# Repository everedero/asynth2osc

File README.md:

# Bad, bad version of the analog synthesizer to Open Sound Control (OSC) module

## Project description

See branch main for the real project description.

On this branch, we modify the working design, to make a test project for automatic review tools.

Do not use it for reference. Do not copy it. Absolutely never send it to production.
This is a design full of mistakes for the sake of finding mistakes.

## Error list

### LAN8742A PHY
* VDDCR is 1.2V LDO output, should not be connected to 3V3.
* nINTSEL/LED2 should be pulled down, to 0. Or we should have a 50 MHz clock instead of 25 MHz.
  * INT/REF\_CLK\_OUT in this schematics look like it is used to generate the 50MHz clock for RMII,
    not as interrupt.
  * LED R80 on the connector should be pulled down to match the inversion.
* RX\_S\_N and RX\_S\_P on U11 (USB ESD diodes) are inverted.
* RBIAS R58 is 51k, it should be 12.1k.

### Interface
* SW7 and SW8 LED has no serial resistor, directly connected to 3V3. Should have a min 68 ohms.
* R82 should be around 1Mohms, not 10k, for the OLED display, as the comment says.

### Supply
* The fuse is short-circuited, net name VBUS should be modified.
* No protection against plugging the Eurorack connector the wrong way round: -12V instead of +12V
  would damage the board. A diode would be great.
* LDO U1 (LM1117M) LCSC reference is for a 5V LDO, it should be a 3V3.

### STM32H7 SoC
* Cannot setup different interrupts for GPIO (EXTI register) having the same numbers but on different ports.
  A comment specifically says the buttons should be interrupts.
    * See [this issue](https://github.com/zephyrproject-rtos/zephyr/issues/45234).
    * Issue with A8 rotative encoder pushbutton VS C8 rotary input B.
    * Issue with D14 rotary input A and E14 trig input.
* Capacitor C23 and C24 should be much lower than 100nF, 4.3pF for instance.
* STM32 NRST pin is not connected, not to a button, not to any debugger pin.
* STM32 Value, RefNum and LCSC number are for the 144 pin version (STM32H723\_Z\_GT instead
  of STM32H723\_V\_GT)

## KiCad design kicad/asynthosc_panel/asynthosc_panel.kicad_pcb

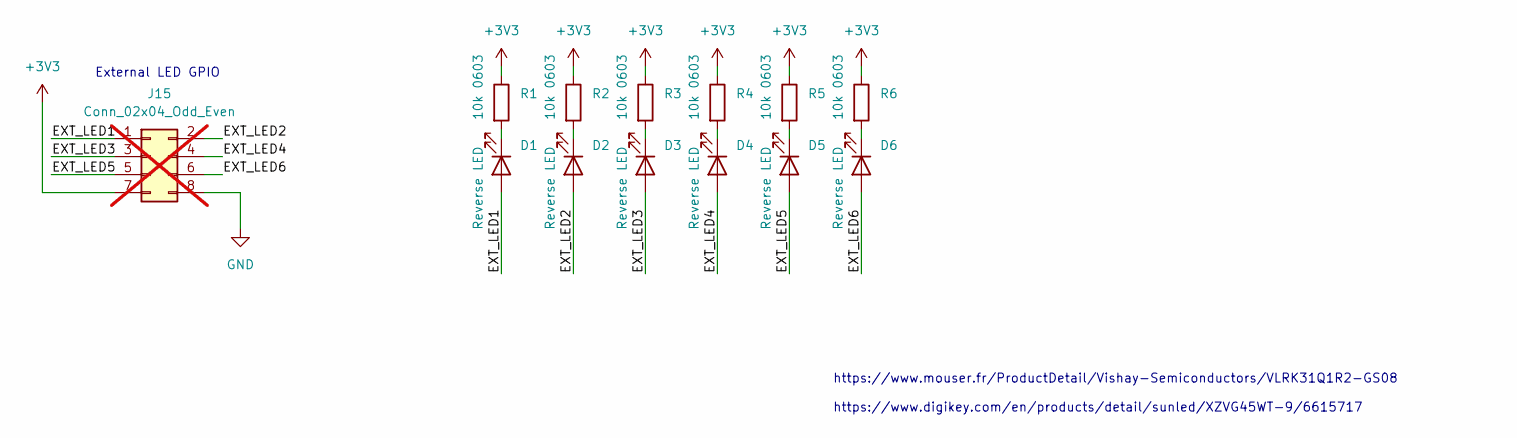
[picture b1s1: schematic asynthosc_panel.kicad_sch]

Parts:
D1, D2, D3, D4, D5, D6: Reverse LED; LED_Sunled_XZxx45x-9_nohole
J15: Conn_02x04_Odd_Even; PinHeader_2x04_P2.54mm_Vertical_SMD; LCSC C192300; not fitted
R1, R2, R3, R4, R5, R6: 10k 0603; R_0603_1608Metric_Pad0.98x0.95mm_HandSolder

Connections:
+3V3: J15.7, R1.1, R2.1, R3.1, R4.1, R5.1, R6.1
/EXT_LED1: D1.2 (A), J15.1
/EXT_LED2: D2.2 (A), J15.2
/EXT_LED3: D3.2 (A), J15.3
/EXT_LED4: D4.2 (A), J15.4
/EXT_LED5: D5.2 (A), J15.5
/EXT_LED6: D6.2 (A), J15.6
GND: J15.8
unnamed: D1.1 (K), R1.2
unnamed: D2.1 (K), R2.2
unnamed: D3.1 (K), R3.2
unnamed: D4.1 (K), R4.2
unnamed: D5.1 (K), R5.2
unnamed: D6.1 (K), R6.2

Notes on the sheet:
https://www.mouser.fr/ProductDetail/Vishay-Semiconductors/VLRK31Q1R2-GS08 https://www.digikey.com/en/products/detail/sunled/XZVG45WT-9/6615717
External LED GPIO

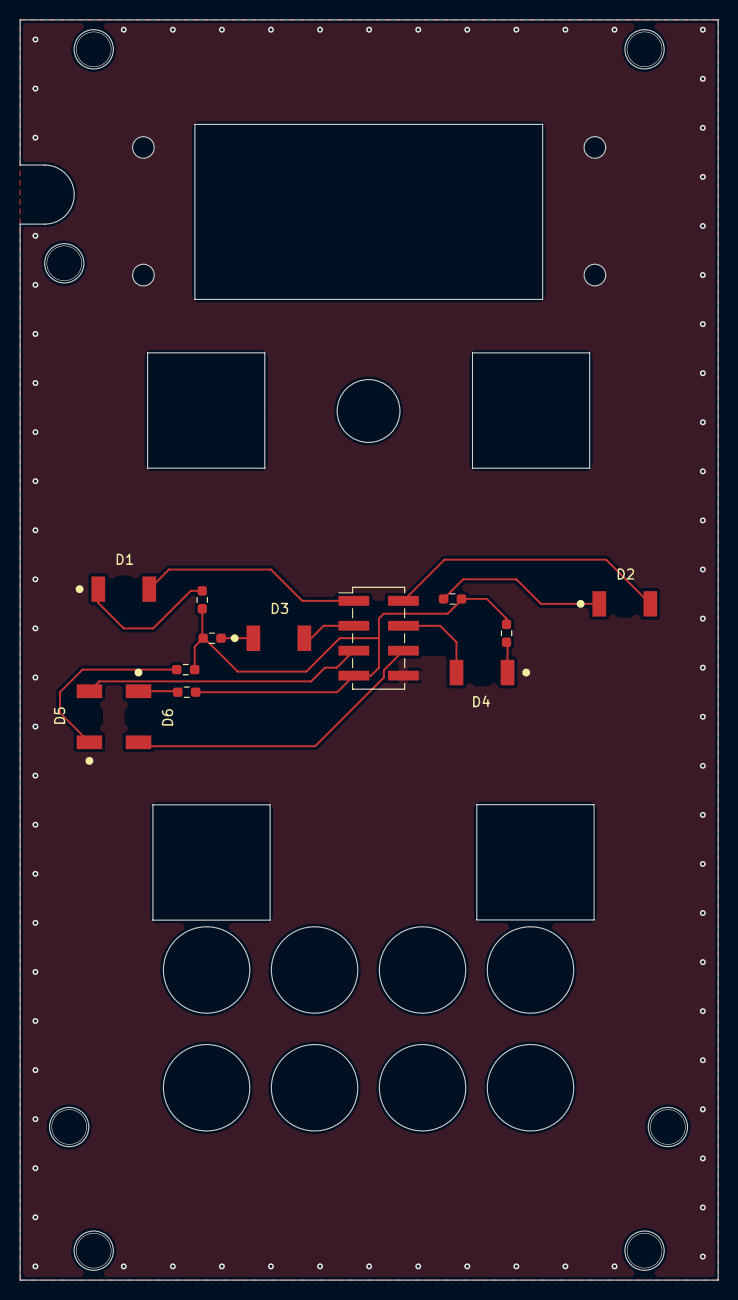
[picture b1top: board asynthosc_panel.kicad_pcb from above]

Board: 2 copper layers, 71.1 x 128.4 mm, 13 parts (0 on the bottom side), 13 nets.

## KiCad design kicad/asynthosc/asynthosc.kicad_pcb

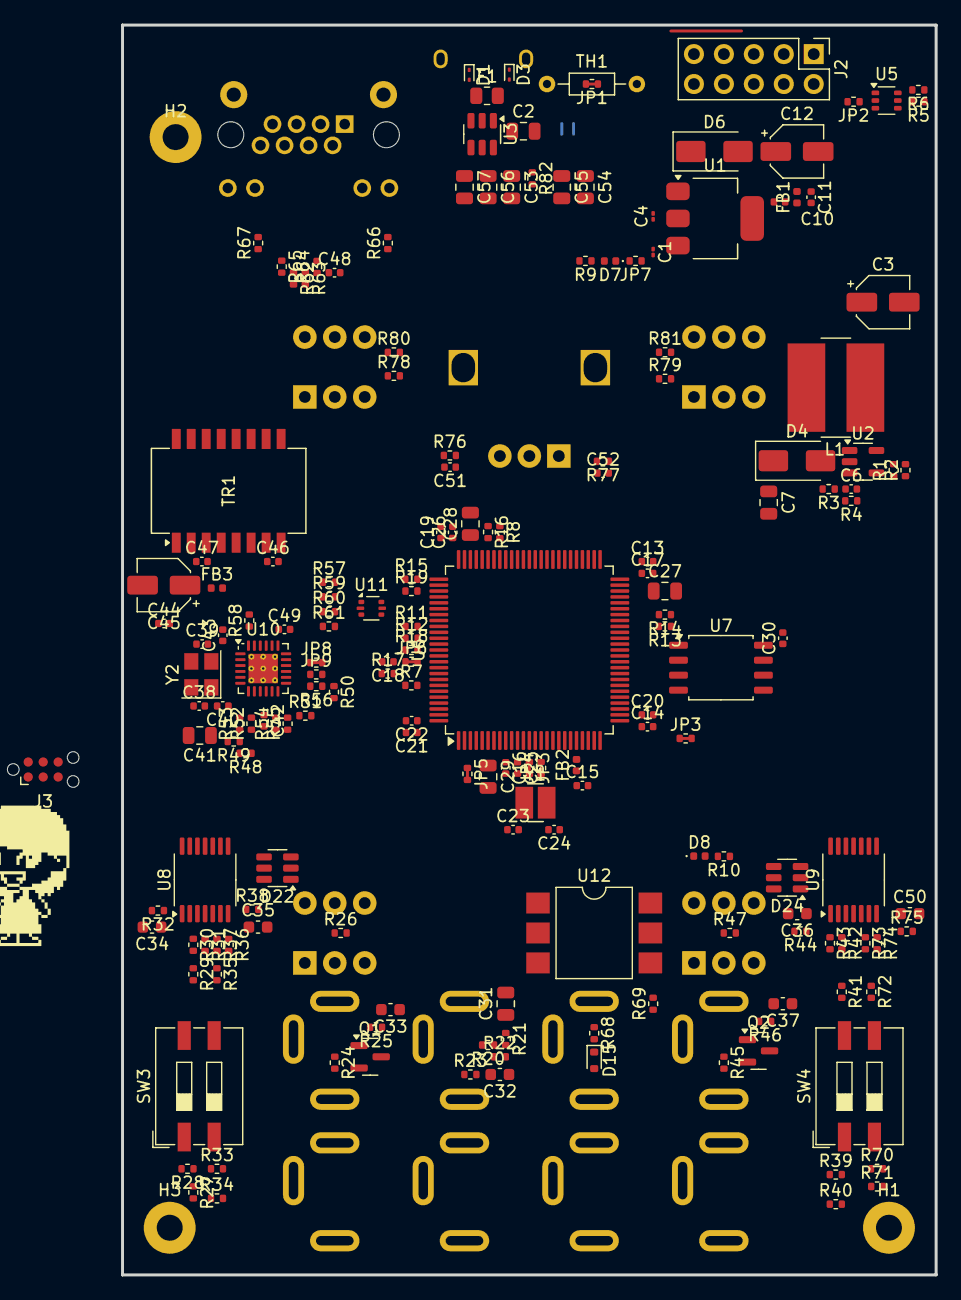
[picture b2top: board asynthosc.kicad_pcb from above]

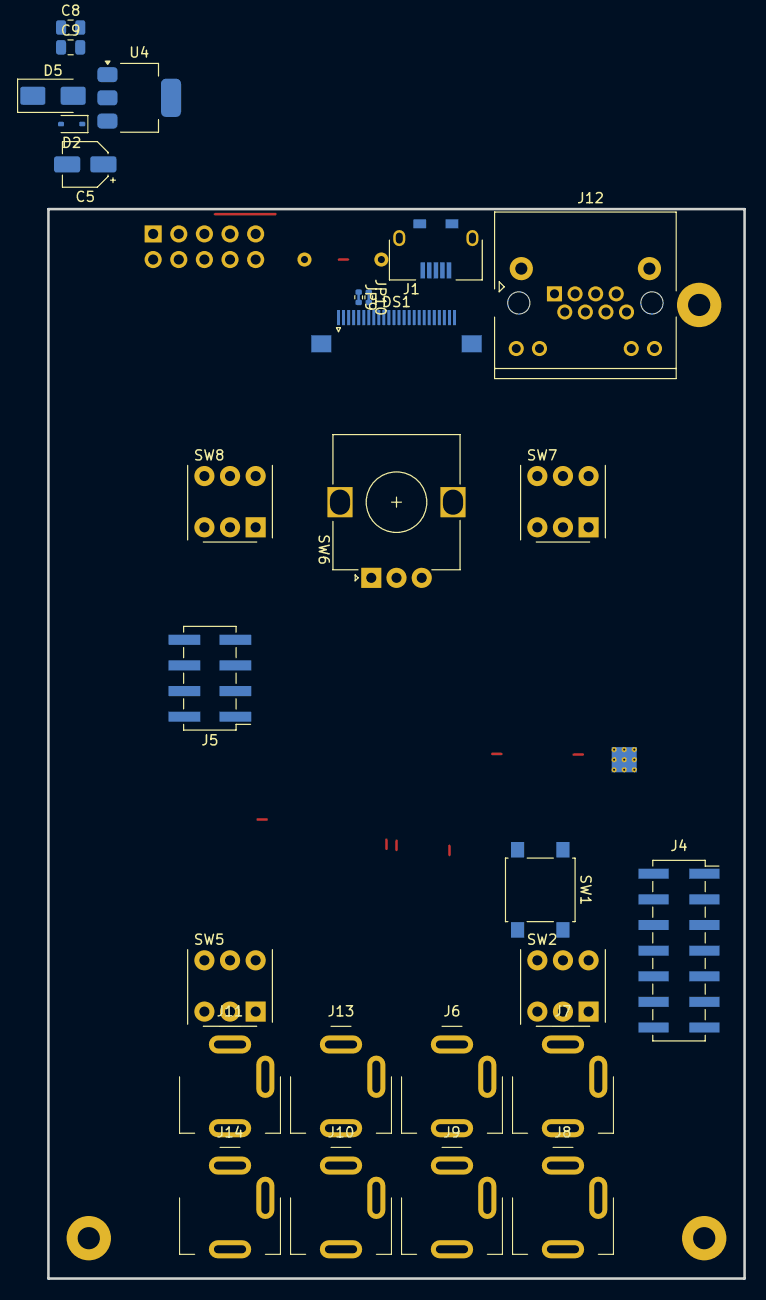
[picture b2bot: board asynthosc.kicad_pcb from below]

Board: 4 copper layers, 69.0 x 106.0 mm, 211 parts (27 on the bottom side), 144 nets, no tracks yet.

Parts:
C1, C4: 100nF; C_01005_0402Metric
C2, C8, C9: 100nF; C_0805_2012Metric
C3, C5, C12, C45: 10uF; CP_Elec_4x5.4
C6: 680pF; C_0402_1005Metric
C7: 47uF / 3.037mOhms; C_0805_2012Metric
C10: 10nF; C_0402_1005Metric
C11, C13, C14, C15, C16, C17, C18, C19, C20, C21, C22, C25, C26, C30, C42, C43, C44, C46, C47, C49, C51, C52: 100nF; C_0402_1005Metric
C23, C24: 4.3pF; C_0402_1005Metric
C27, C28: 2.2u X7R; C_0805_2012Metric
C29, C41: 1uF; C_0805_2012Metric
C31: 10uF; C_0805_2012Metric
C32: 18pF; C_0603_1608Metric
C33, C37: 100nF; C_0603_1608Metric
C34, C35, C36, C50: 1nF; C_0603_1608Metric
C38, C39: 30pF; C_0402_1005Metric
C40: 470pF; C_0402_1005Metric
C48: 1000pF X7R; C_0402_1005Metric
C53: 2.2uF/25V; C_0805_2012Metric
C54, C55: 1uF / 16V; C_0805_2012Metric
C56: 4.7uF/25V/X7R; C_0805_2012Metric
C57: 0.1uF/25V/X7R; C_0805_2012Metric
D1, D3: ESD9B5.0ST5G; D_SOD-923
D2: 1N5819WS; D_SOD-323
D4, D5, D6: SS24; D_SMA
D7, D8: LED; LED_0402_1005Metric
D15: 1N4148WT; D_SOD-523
D22, D24: D_Schottky_Dual_SD103ASDM; SOT-23-6
DS1: OLED Connector 128x64; HRO_FPC0.5B-WTG-24P_1x24-1MP_P0.5mm_Horizontal
F1: Fuse, 1.25A, trip 2.5A; R_0805_2012Metric
FB1, FB2, FB3: BLM15PX330SN1D; L_0402_1005Metric
H1, H2, H3: MountingHole_Pad; MountingHole_2.2mm_M2_Pad
J1: USB_B_Micro; USB_Micro-B_Shou-han-MicroXNJ
J2: Conn_02x05_Odd_Even; PinHeader_2x05_P2.54mm_Vertical
J3: Conn_ARM_SWD_TagConnect_TC2030-NL; Tag-Connect_TC2030-IDC-NL_2x03_P1.27mm_Vertical
J4: Conn_02x07_Odd_Even; PinSocket_2x07_P2.54mm_Vertical_SMD
J5: Conn_02x04_Odd_Even; PinHeader_2x04_P2.54mm_Vertical_SMD
J6, J7, J8, J9, J10, J11, J13, J14: AudioJack3; Jack_3.5mm_3legs_XKB_PJ-3411_Vertical
J12: RJ45_LED_Shielded; RJ45_HCTL_HC-RJ45-053-2
JP1, JP3, JP3#2, JP4, JP5, JP6, JP8, JP9#2, JP10: SolderJumper_2_Bridged; SolderJumper_0402_1005Metric_Bridged
JP2, JP7, JP9: SolderJumper_2_Open; R_0402_1005Metric
L1: 8.2uH / 80mOhm; L_XR_XRCD75-XRX_7x7.8
Q1, Q2: Q_NPN_BEC; SOT-23
R1, R2, R3, R5, R6, R8, R25, R46, R76, R77, R78, R79: 10k; R_0402_1005Metric
R4: 69.8k; R_0402_1005Metric
R7, R24, R29, R30, R35, R36, R41, R42, R45, R48, R49, R50, R72, R73: 100k; R_0402_1005Metric
R9, R10, R26, R47, R66, R67, R80, R81: 270R; R_0402_1005Metric
R11, R12, R13, R14, R15, R16, R17, R18, R19: 22R; R_0402_1005Metric
R20, R22: 39k; R_0402_1005Metric
R21: 5.6k; R_0402_1005Metric
R23: 1k; R_0402_1005Metric
R27, R33, R39, R70: 47k; R_0402_1005Metric
R28, R31, R32, R34, R37, R38, R40, R43, R44, R71, R74, R75: 33k; R_0402_1005Metric
R51: 1.5K; R_0402_1005Metric
R52, R53, R54, R55, R56: 33R; R_0402_1005Metric
R57, R59, R60, R61: 50R; R_0402_1005Metric
R58: 12.1k; R_0402_1005Metric
R62, R63, R64, R65: 75R; R_0402_1005Metric
R68, R69: 220; R_0402_1005Metric
R82: 1M; R_0402_1005Metric
SW1: SW_Push; SW_SPST_B3S-1000
SW2, SW5, SW7, SW8: SW_MEC_5G_LED; TPB01-X0XLXX_SW_MEC_5G
SW3, SW4: SW_DIP_x02; SW_DIP_SPSTx02_Slide_9.78x7.26mm_W8.61mm_P2.54mm
SW6: RotaryEncoder; RotaryEncoder_Alps_EC12E_Vertical_H20mm
TH1: Thermistor_NTC; R_Axial_DIN0204_L3.6mm_D1.6mm_P7.62mm_Horizontal
TR1: PT61017PEL; Transformer_Ethernet_Bourns_PT61017PEL
U1: LM1117S-3.3; SOT-223
U2: LMR62421XMF; SOT-23-5
U3: USBLC6-2SC6; SOT-23-6
U4: LM1117S-5.0; SOT-223
U5: Si1869DH; SOT-363_SC-70-6
U6: STM32F723VETx; LQFP-100_14x14mm_P0.5mm
U7: W25Q32JVSS; SOIC-8_5.23x5.23mm_P1.27mm
U8, U9: MCP6004; TSSOP-14_4.4x5mm_P0.65mm
U10: LAN8742A; VQFN-24-1EP_4x4mm_P0.5mm_EP2.5x2.5mm_ThermalVias
U11: USBLC6-2P6; SOT-666
U12: H11L1; SMDIP-6_W9.53mm
Y1: 8MHz, 8pF; Crystal_SMD_3225-2Pin_3.2x2.5mm
Y2: 25MHZ,20PF,30PPM; Crystal_SMD_3225-4Pin_3.2x2.5mm

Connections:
3V3: C4.1, C13.1, C14.1, C15.1, C16.1, C17.1, C19.1, C20.1, C21.1, C22.1, C25.1, C26.1, C30.1, C40.1, C41.1, C42.1, C54.1, C55.1, D22.2 (K), D22.5 (K), D24.2 (K), D24.5 (K), DS1.5 (VDD), FB2.1, FB3.2, J3.1 (VCC), J4.2, JP5.2 (B), R9.1, R10.1, R25.2, R46.2, R48.2, R49.2, R50.2, R51.2, R69.1, R76.1, R77.1, R78.1, R79.1, R80.1, R81.1, U1.2 (VO), U6.11 (VDD), U6.27 (VDD), U6.50 (VDD), U6.75 (VDD), U6.100 (VDD), U7.8 (VCC), U10.6 (VDDCR), U10.9 (VDDIO), U12.6
3V3_FILT: C43.1, C44.1, C45.1, C46.1, C47.1, C49.1, FB3.1, R57.2, R59.2, R60.2, R61.2, TR1.2 (C_TD), TR1.7 (C_RD), U10.1 (VDD2A), U10.19 (VDD1A), U11.5 (VBUS)
5V: C1.1, D5.1 (K), D6.1 (K), R30.2, R36.2, R42.2, R73.2, U1.3 (VI), U8.4 (V+), U9.4 (V+)
+10V: C6.2, C7.1, C56.1, C57.1, D4.1 (K), DS1.23 (VCC), JP2.2 (B), R4.1
/Analog_in/CVIN0: C34.1, D22.6 (common), R32.1, U6.22 (PA0), U8.1
/Analog_in/CVIN1: C35.1, D22.3 (common), R38.1, U6.25 (PA3), U8.7
/Analog_in/CVIN2: C36.1, D24.6 (common), R44.1, U6.29 (PA5), U9.1
/Analog_in/CVIN3: C50.1, D24.3 (common), R75.1, U6.30 (PA6), U9.7
/Analog_in/TRG0: C37.2, Q2.3 (C), R46.1, SW5.1, SW5.3 (K)
/Analog_in/TRG1: C33.2, Q1.3 (C), R25.1, SW2.1, SW2.3 (K), U6.43 (PE13)
/Interface/BTN_1: R78.2, SW7.1
/Interface/BTN_2: R79.2, SW8.1
/Interface/ROT_A: C52.1, R77.2, SW6.A
/Interface/ROT_B: C51.1, R76.2, SW6.B
/Interface/SCLK: DS1.13 (D0), U6.78 (PC10)
/Interface/SDIN: DS1.14 (D1), U6.80 (PC12)
/Midi_in/MIDI_IN+: J13.R, R68.1
/Midi_in/MIDI_IN-: D15.2 (A), J13.T, U12.2
/Midi_in/MIDI_TO_SOC: R69.2, U12.4
/Soc/BOOT0: R7.2, U6.94 (BOOT0)
/Soc/DAC_OUT1: C31.2, U6.28 (PA4)
/Soc/DISP_10V_EN: R1.1, R2.1, U2.4 (EN)
/Soc/Ethernet/RJ45_LED1: J12.12, U10.3 (LED1/REGOFF)
/Soc/Ethernet/RJ45_LED2: J12.10, U10.2 (LED2/~INTSEL)
/Soc/Ethernet/RJ_RX_N: J12.6, R62.2, TR1.15 (C_TX)
/Soc/Ethernet/RJ_RX_P: J12.3, TR1.14 (TX-)
/Soc/Ethernet/RJ_TX_N: J12.2, TR1.11 (RX+)
/Soc/Ethernet/RJ_TX_P: J12.1, TR1.9 (RX-)
/Soc/Ethernet/RX_N: R57.1, TR1.1 (TD+), U10.22 (RXN), U11.6 (I/O1)
/Soc/Ethernet/RX_P: R59.1, TR1.3 (TD-), U10.23 (RXP), U11.1 (I/O1)
/Soc/Ethernet/TX_N: R60.1, TR1.6 (RD+), U10.20 (TXN), U11.4 (I/O2)
/Soc/Ethernet/TX_P: R61.1, TR1.8 (RD-), U10.21 (TXP), U11.3 (I/O2)
/Soc/JTCK: R15.2, U6.76 (PA14)
/Soc/JTCK_CONN: J3.4 (SWCLK), J4.4, R15.1
/Soc/JTDI: R19.2, U6.77 (PA15)
/Soc/JTDI_CONN: J4.14, R19.1
/Soc/JTDO: R18.2, U6.89 (PB3)
/Soc/JTDO_CONN: J3.6 (SWO), J4.12, R18.1
/Soc/JTMS: R16.2, U6.72 (PA13)
/Soc/JTMS_CONN: J3.2 (SWDIO), J4.8, R16.1
/Soc/NRST: C18.1, JP6.1 (A), JP8.2 (B), R17.2, SW1.2, U6.14 (NRST)
/Soc/NRST_CONN: J3.3 (~RESET), J4.10, R17.1
/Soc/QSPI_BK2_IO0: U6.18 (PC3), U7.5 (DI(IO0))
/Soc/QSPI_BK2_IO1: U6.34 (PB0), U7.2 (DO(IO1))
/Soc/QSPI_BK2_IO2: U6.1 (PE2), U7.3 (IO2)
/Soc/QSPI_BK2_IO3: U6.60 (PD13), U7.7 (IO3)
/Soc/QSPI_BK2_NCS: U6.41 (PE11), U7.1 (~CS)
/Soc/QSPI_CLK: U6.36 (PB2), U7.6 (CLK)
/Soc/RMII_CRS_DV: R55.1, U6.31 (PA7)
/Soc/RMII_MDC: U6.16 (PC1), U10.13 (MDC)
/Soc/RMII_MDIO: R51.1, U6.24 (PA2), U10.12 (MDIO)
/Soc/RMII_REF_CLK: R50.1, R56.1, U6.23 (PA1)
/Soc/RMII_RXD0: R48.1, R52.1, U6.32 (PC4)
/Soc/RMII_RXD1: R49.1, R53.1, U6.33 (PC5)
/Soc/RMII_TXD0: U6.51 (PB12), U10.17 (TXD0)
/Soc/RMII_TXD1: U6.52 (PB13), U10.18 (TXD1)
/Soc/RMII_TX_EN: R14.2, U6.47 (PB11), U10.16 (TXEN)
/Soc/USART2_DBG_RX: R11.2, U6.87 (PD6)
/Soc/USART2_DBG_TX: R12.2, U6.86 (PD5)
/Soc/USART3_BOOT_DBG_TX: R13.2, U6.46 (PB10)
/Soc/USB_D_N: U3.4 (I/O2), U6.70 (PA11)
/Soc/USB_D_P: U3.6 (I/O1), U6.71 (PA12)
/Soc/USB_ID: D3.2 (A2), J1.4 (ID), U6.69 (PA10)
/Soc/VDDA: FB2.2, U6.20 (VREF+), U6.21 (VDDA)
/Supply/5V_CLEAN: C11.1, C12.1, D6.2 (A), FB1.2
/Supply/5V_EUR: C9.1, D5.2 (A), U4.2 (VO)
/Supply/DISP_12V_EN: R5.2, U5.5 (ON)
/Supply/EUR_+12V: D2.2 (A), J2.1, J2.2
/Supply/EUR_-12V: J2.9, J2.10
/Supply/IN_+12V: C5.1, C8.1, D2.1 (K), R6.1, U4.3 (VI), U5.4 (IN)
/Supply/USBIN_D_N: J1.2 (D-), U3.3 (I/O2)
/Supply/USBIN_D_P: J1.3 (D+), U3.1 (I/O1)
/Supply/VBUS: C2.1, C3.1, D1.2 (A2), F1.1, J1.1 (VBUS), L1.1, R1.2, R8.1, U2.5 (VIN), U3.5 (VBUS)
GND: C1.2, C2.2, C3.2, C4.2, C5.2, C7.2, C8.2, C9.2, C10.2, C11.2, C12.2, C13.2, C14.2, C15.2, C16.2, C17.2, C18.2, C19.2, C20.2, C21.2, C22.2, C23.1, C24.1, C25.2, C26.2, C27.2, C28.2, C29.2, C30.2, C33.1, C37.1, C38.1, C39.1, C40.2, C41.2, C42.2, C43.2, C44.2, C45.2, C46.2, C47.2, C48.2, C49.2, C51.2, C52.2, C53.2, C54.2, C55.2, C56.2, C57.2, D1.1 (A1), D3.1 (A1), D22.1 (A), D22.4 (A), D24.1 (A), D24.4 (A), DS1.1 (GND), DS1.2 (VLSS), DS1.3 (VSS), DS1.11 (R/~W), DS1.12 (E/~RD), DS1.16 (D3), DS1.17 (D4), DS1.18 (D5), DS1.19 (D6), DS1.20 (D7), DS1.24 (GND), H1.1, H2.1, H3.1, J1.5 (GND), J1.6 (Shield), J2.3, J2.4, J2.5, J2.6, J2.7, J2.8, J3.5 (GND), J4.1, J4.3, J4.5, J4.6, J4.7, J4.9, J4.11, J4.13, J5.4, J5.5, J6.S, J7.S, J8.S, J9.S, J10.S, J11.S, J12.SH, J14.S, JP3#2.2 (B), JP7.1 (A), JP9#2.1 (A), JP10.1 (A), Q1.2 (E), Q2.2 (E), R2.2, R3.2, R5.1, R7.1, R20.2, R26.2, R28.2, R31.2, R34.2, R37.2, R40.2, R43.2, R47.2, R54.1, R58.2, R66.1, R67.1, R71.2, R74.2, R82.2, SW1.1, SW2.4 (A), SW5.4 (A), SW6.C, SW7.4 (A), SW8.4 (A), U1.1 (GND), U2.2 (GND), U3.2 (GND), U4.1 (GND), U5.1 (R2), U6.10 (VSS), U6.19 (VSSA), U6.26 (VSS), U6.49 (VSS), U6.74 (VSS), U6.99 (VSS), U7.4 (GND), U8.9 (-), U8.11 (V-), U9.11 (V-), U10.25 (VSS), U11.2 (GND), U12.5
unnamed: C31.1, R20.1, R21.2
unnamed: C32.2, R22.1, R23.2, U8.8
unnamed: C48.1, R62.1, R63.1, R64.1, R65.1
unnamed: D4.2 (A), L1.2, U2.1 (SW)
unnamed: D7.2 (A), R9.2
unnamed: D7.1 (K), JP7.2 (B)
unnamed: D8.2 (A), R10.2
unnamed: D15.1 (K), R68.2, U12.1
unnamed: DS1.6 (BS1), JP9#2.2 (B)
unnamed: DS1.7 (BS2), JP10.2 (B)
unnamed: DS1.21 (IREF), R82.1
unnamed: C53.1, DS1.22 (VCOMH)
unnamed: J5.1, R11.1
unnamed: J5.2, R13.1
unnamed: J5.7, R12.1
unnamed: J5.8, R14.1
unnamed: J6.T, R23.1
unnamed: J7.T, R24.2
unnamed: J8.T, R27.2, SW3.1
unnamed: J10.T, R39.2, SW4.1
unnamed: J11.T, R45.2
unnamed: J12.4, J12.5, R64.2
unnamed: J12.7, J12.8, R65.2
unnamed: J12.9, R66.2
unnamed: J12.11, R67.2
unnamed: F1.2, JP1.1 (A), TH1.1
unnamed: C10.1, FB1.1, JP1.2 (B), TH1.2
unnamed: JP2.1 (A), U5.2 (OUT), U5.3 (OUT)
unnamed: JP3.1 (A), U6.12 (PH0)
unnamed: C23.2, JP3.2 (B), Y1.2
unnamed: JP4.1 (A), U6.13 (PH1)
unnamed: C24.2, JP4.2 (B), Y1.1
unnamed: C29.1, JP5.1 (A), U6.6 (VBAT)
unnamed: JP6.2 (B), U6.90 (PB4)
unnamed: JP8.1 (A), U10.15 (~RST)
unnamed: Q1.1 (B), R24.1
unnamed: Q2.1 (B), R45.1
unnamed: R26.1, SW2.2
unnamed: R47.1, SW5.2
unnamed: R27.1, R28.1, R29.2, SW3.4 (2)
unnamed: J9.T, R33.2, SW3.2 (1)
unnamed: R33.1, R34.1, R35.2, SW3.3 (2)
unnamed: R39.1, R40.1, R41.2, SW4.4 (2)
unnamed: J14.T, R70.2, SW4.2 (1)
unnamed: R70.1, R71.1, R72.2, SW4.3 (2)
unnamed: R80.2, SW7.3 (K)
unnamed: R81.2, SW8.3 (K)
unnamed: R63.2, TR1.10 (C_RX)
unnamed: C6.1, R3.1, R4.2, U2.3 (FB)
unnamed: R6.2, U5.6 (R1)
unnamed: R8.2, U6.68 (PA9)
unnamed: C27.1, U6.48 (VCAP_1)
unnamed: C28.1, U6.73 (VCAP_2)
unnamed: R30.1, R31.1, U8.3 (+)
unnamed: C34.2, R29.1, R32.2, U8.2 (-)
unnamed: R36.1, R37.1, U8.5 (+)
unnamed: C35.2, R35.1, R38.2, U8.6 (-)
unnamed: C32.1, R21.1, R22.2, U8.10 (+)
unnamed: R42.1, R43.1, U9.3 (+)
unnamed: C36.2, R41.1, R44.2, U9.2 (-)
unnamed: R73.1, R74.1, U9.5 (+)
unnamed: C50.2, R72.1, R75.2, U9.6 (-)
unnamed: R55.2, U10.11 (CRS_DV/MODE2)
unnamed: R58.1, U10.24 (RBIAS)
unnamed: R52.2, U10.8 (RXD0/MODE0)
unnamed: R53.2, U10.7 (RXD1/MODE1)
unnamed: R54.2, U10.10 (RXER/PHYAD0)
unnamed: C38.2, U10.5 (XTAL1/CLKIN), Y2.1
unnamed: C39.2, U10.4 (XTAL2), Y2.2
unnamed: R56.2, U10.14 (~INT/REFCLKO)

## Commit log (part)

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2024-01-17 doc: add readme
2024-01-23 doc: update
2024-01-23 doc: adding a draft bom
2024-05-05 wip: update bom and description
2024-05-05 start diagram
2024-05-05 add ldo
2024-05-20 wip: STM32 architecture option
2024-05-20 wip: esp32 bom update
2024-05-20 bom stm32
2024-05-21 doc: add dac comparison, fix architecture drawing with stm32
2024-06-09 bom: optional 100-pins stm32
2024-08-02 sch: add kicad files
2024-08-02 doc: update readme
2024-08-02 sch: wip, add .gitignore
2024-08-06 sch: wip
2024-08-06 sch: basic stm32 with power, clocks and debug
2024-08-06 sch: rmii side
2024-08-07 sch: top sheet pins input
2024-08-08 comp: add new componant libraries
2024-08-08 sch: update and new interface sheet
2024-08-08 doc: midi
2024-08-08 cleanup: project temp files
2024-08-08 comp: add jack footprints
2024-08-09 doc: update readme with more eurorack info
2024-08-09 sch: add spi nor, display connection, and more footprints
2024-08-09 sch: power supply improvements
2024-08-09 comp: new component
2024-08-09 sch: update footprint links
2024-08-13 sch: change stm32 for smaller one, create smaller jumper footprint
2024-08-13 bom: update bom for lcsc
2024-08-13 sch: dip switch with separated sym
2024-08-13 [sch][brd] Fix RJ45 footprint
2024-08-13 brd: move connectors to bot (components will be on bottom, connectors on top)
2024-09-01 pcb: placing
2024-09-01 pcb: place and change some components for easier routing
2024-09-17 pcb: moving graphical elements
2024-09-17 wip: place
2024-09-17 pcb: place and draft route
2024-09-17 pcb: routing wip
2024-09-17 pcb: routing
2024-09-17 pcb: route
2024-09-17 sch: pcb: tiny fixes and changes
2024-09-17 sch: pcb: fix pin errors
2024-09-17 sch: pcb: add gpio output connector for optional LEDs on decorative board
2024-09-17 sch: pcb: fix: footprint mismatches
2024-09-17 sch: pcb: wip and silkscreen cleaning
2024-09-17 pcb: route, add some silkscreen
2024-09-17 pcb: fix mechanical issues after easyeda simulation
2024-09-17 pcb: beautify
2024-09-17 pcb: sch: drown mp pad in gnd for display connector
2024-09-17 pcb: configure jlc 4-layer stackup
2024-09-17 sch: alternative displays. pcb: wip
2024-09-17 drc: fix min via crown size
2024-09-17 pcb: add diff pair values
2024-09-17 comp: add vertical usb micro-b and rj45 footprints
2024-09-17 pcb: change connectors
2024-09-17 pcb: fix some more drc
2024-09-17 pcb: fix some drc
2024-09-17 pcb: sch: panel: add panelisation for pcba assembly
2024-09-17 pcb: drc and antenna fix
2024-09-17 pcb: fix drc
2024-09-17 pcb: add panelization
2024-09-17 gitignoring kicad_prl file
2024-09-17 pcb: add design rules to match jlc pcba assembly rules. sch: fix a 0805 package mishap
2024-09-17 bom: sch: pcb: update for sourcing in jlc pcba services
2024-09-17 bom: update mfr, serials and lcsc fields
2024-09-17 sch: change stm32 ref for adc
2024-09-17 pcb: board outline and milling update
2024-09-17 bom: update for better bom
2024-09-17 pcb: change export option for jlc
2024-09-17 pcb: update drc from jlc
2024-09-17 pcb: export place file
2024-09-17 sch: pcb: change stm32 gpio pinout to h7
2024-09-17 dru: ignore thermal pads in th rule
2024-09-17 pcb: more design rules
2024-09-17 pcb: drc draft
2024-09-17 bom: add jlcpcb field with simplified footprint
2024-09-17 sch: add no connect indicators
2024-09-17 pcb: drc
2024-09-17 bom: remove non-equiped components from bom and assembly guide
2024-09-17 lib: change component reference to match jlc
2024-09-17 pcb: wip, moving components again
2024-09-17 pcb: replace display connector
2024-09-17 pcb: update
2024-09-17 pcb: wip
2024-09-17 pcb: bom: comp: misc fixes, button footprint, and move usb-b away from rj45
2024-09-17 bom: dnp for all manually equiped components
2024-09-17 cleanup: ignore csv and xml in project folder
2024-09-17 doc: update readme with jlc export trick
2024-09-18 doc: review todo
2024-09-18 doc: add review document
2024-09-18 sch: pcb: add a diode for external 5V input to protect USB VBUS
2024-09-19 fix: qspi ncs port issue, port naming
2024-09-19 fix: dividor bridge for usb vbus input sensing
2024-09-19 doc: update todo
2024-09-19 fix: put all components after fuse
2024-09-19 fix: divider bridge stupid mistake
2024-09-19 doc: power consumption estimates
2024-09-19 fix: ldo tab is vout
2024-09-19 pcb: wip: update from sch fixes
2024-09-20 doc: todo
2024-09-23 drc: create a via not close enough to pad detection
2024-09-24 doc: wip file update
2024-09-24 fix: ethernet stage pull-up resistors
2024-09-24 fix: ethernet filtering capacitor size
2024-09-24 schlib: update footprint regexp
2024-09-24 sch: add decoupling capacitor to 10V switch
2024-09-24 sch: nc to gnd
2024-09-25 footprint: add mechanical hole to buttons
2024-09-25 remove duplicate footprint
2024-09-25 sch: modifs on supply
2024-09-25 bom: adding jlc ref to generic
2024-09-25 bom: update led footprint
2024-09-25 doc: update list
2024-09-25 bom: change bom export options
2024-09-26 bom: update jlcpcb part numbers
2024-09-27 sch: bom: fix footprints and bom
2024-09-27 fix: footprint: button is polarized, fix led according to easyeda footprint
2024-09-27 wip: pcb
2024-09-27 sch: decoupling to aop
2024-09-27 pcb: wip decoupling
2024-09-28 doc: update review
2024-09-28 wip: pcb review
2024-09-28 doc: review
2024-09-29 sch: update bom
2024-09-29 pcb: update routing
2024-09-29 pcb: add more via stitching
2024-09-30 simu: ignore component in simulation
2024-10-28 lib: add jack 3d model
2024-10-30 3d: add 3d file folder
2024-10-30 lib: add new 3d to footprint lib
2024-10-30 pcb: update 3d links
2024-10-30 3d: move drill to user 3 layer and redraw final pcb shape
2024-11-04 bom: fab: switch component due to fab shortage
2024-11-10 doc: price breakdown
2024-11-11 doc: add rotation file for jlc-kicad-tools
2024-11-11 cleanup: remove work temp work files
2024-11-16 doc: add firmware readme
2024-11-19 panel: add cover panel draft
2024-11-19 doc: update readme with first bringup notes
2024-11-25 doc: wip
2025-01-19 doc: readme update
2025-01-19 doc: update fw folder readme to link to the repo
2025-01-20 readme: update bringup notes
2025-01-24 doc: update bringup
2025-02-09 doc: fix: bringup notes, phy led2 should be pulled down
2025-02-11 wip: bringup notes
2025-03-14 doc: move bringup todo in the readme
2025-03-14 doc: update readme with bringup
2025-03-17 doc: readme: bringup test update with 12V ext check
2025-03-22 add panel files
2025-03-23 doc: first cnc run doc
2025-03-25 fix: better dimensions
2025-05-02 sch: phy fixes on ldo and leds
2025-05-02 pcb: wip breaking wrong nets
2025-05-02 sch: bump to kicad 9
2025-05-02 sch: update footprint for kicad9
2025-05-02 clean: rename untitled as midi_in
2025-05-02 sch: add power directive on ldo in
2025-05-02 sch: update to k9 libs, fix nets
2025-05-02 pcb: current fixes, update to 0.2
2025-05-02 panel: add freecad design with cnc
2025-05-02 panel: update pcb
2025-05-30 doc: add images
2025-05-30 pouet
2025-08-28 cleanup: file not belonging in repo
2025-10-20 DXF autocad version export
2025-11-10 breaking schematics to trigger erc
2026-03-30 Update README with MIDI TRS connector details
    Added information about MIDI type A and type B standards.
2026-03-30 doc: more details on nINTSEL
2026-05-04 Add GitHub Pages site with images
2026-05-04 Fix GitHub repository URLs to madees/asynth2osc
2026-05-17 [CLEANUP] No prompt
2026-05-17 [CLEANUP] Move all images in same folder
2026-05-17 [DOC] Pages website (#6)
    * Add GitHub Pages site with images
    * Move GitHub repository URLs to madees/asynth2osc
    * [CLEANUP] No prompt
    * [CLEANUP] Move all images in same folder
2026-05-17 Refine asynthosc panel artwork
2026-05-18 lib: bump to v9
2026-05-18 lib: invisible pin fix
2026-05-18 sch: update component
2026-05-18 [MECA] Add 1mm milling contour
2026-05-18 [LIB] Add footprint lib to panel project
2026-05-18 [FOOT] Add corrupt LED footprint
2026-05-18 [SCH][PCB] Add connector and LEDs
2026-05-18 [FOOT] Add Sunled reverse-mount footprint
2026-05-18 [FOOT] Rename footprint to match manuf name
2026-05-19 [PCB] Add slot for cable
2026-05-19 [PCB] Add mounting hole for display holder
2026-05-19 [FOOT] Add asynthosc logo
2026-05-19 [FOOT] WIP cat logo
2026-05-19 [SCH] Link footprint lib
2026-05-19 [SCH] Update LED model
2026-05-19 [FOOT] Add the LED without hole
2026-05-19 [CLEANUP] Add gitignore
2026-05-19 [PCB] Bit of cleanup
2026-05-19 [FOOT] Reversed cat
2026-05-19 [FOOT] Flowers
2026-05-19 [FOOT] Cat updated
2026-05-20 [PCB] Integrate new design
2026-05-21 [FOOT] Change cats contour to silkscreen
2026-05-21 [DRU] Import design rules
2026-05-21 [PANEL] Decorative stuff
2026-05-21 [PCB] Contours
2026-05-21 [PRJ] Design rules
2026-05-21 [FIX][PCB] Amost all DRU
2026-05-21 [WIP] PCB
2026-05-21 [PANEL] Update front panel (#8)
    With crazy footprints for see-through reverse LEDs
2026-05-28 [DOC] Reverse LED options

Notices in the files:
kicad/asynthosc/asynthosc.kicad_pcb:
CERN Open Hardware Licence
